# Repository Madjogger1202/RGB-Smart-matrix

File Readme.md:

# RGB-Matrix-SM16306

> 8×16 RGB LED matrix based on **SM16306SJ constant-current drivers**.  
> Designed as a cost-effective alternative to addressable LED panels.  

---

## Motivation
When working on a previous badge project, it became clear that building matrices out of addressable LEDs (e.g. WS2812) quickly becomes too expensive.  
The solution: use **standard RGB LEDs** combined with **constant-current drivers**.  

---

## Hardware Overview
- **LEDs**: XL-B1010RGBT-HF  
- **Matrix size**: 8 × 16 (128 RGB = 384 channels)  
- **Drivers**: SM16306SJ  
  - 16 constant-current channels per chip  
  - Current per channel: **20 mA**  
- **Row control**: standard shift register + power switches for row selection  
- **Power budget**:  
  - up to **34 LEDs per row**  
  - peak current up to **2 A per row**  

---

## Key Points
- At least **5× cheaper** compared to addressable LED matrices.  
- **Accurate current driving** ensures stable brightness and color balance.  
- Easily scalable for larger panels.  
- Requires an external **controller** (e.g. RP2040, ESP32) to drive shift registers and SM16306SJ chips.  

---

## PCB Notes
- Initial goal: a **two-sided layout**  
  - LEDs on the front  
  - Drivers + shift registers on the back  
- In practice: all components ended up on the same side to simplify routing.  
- Possible future version: **two-board design** (LED front panel + driver board).  

---

## Next Steps
- Integrate this matrix into the upcoming **badge version**.  
- Provide example firmware (SPI driving + timing).  
- Test long-term reliability at **20 mA per channel** load.  

---

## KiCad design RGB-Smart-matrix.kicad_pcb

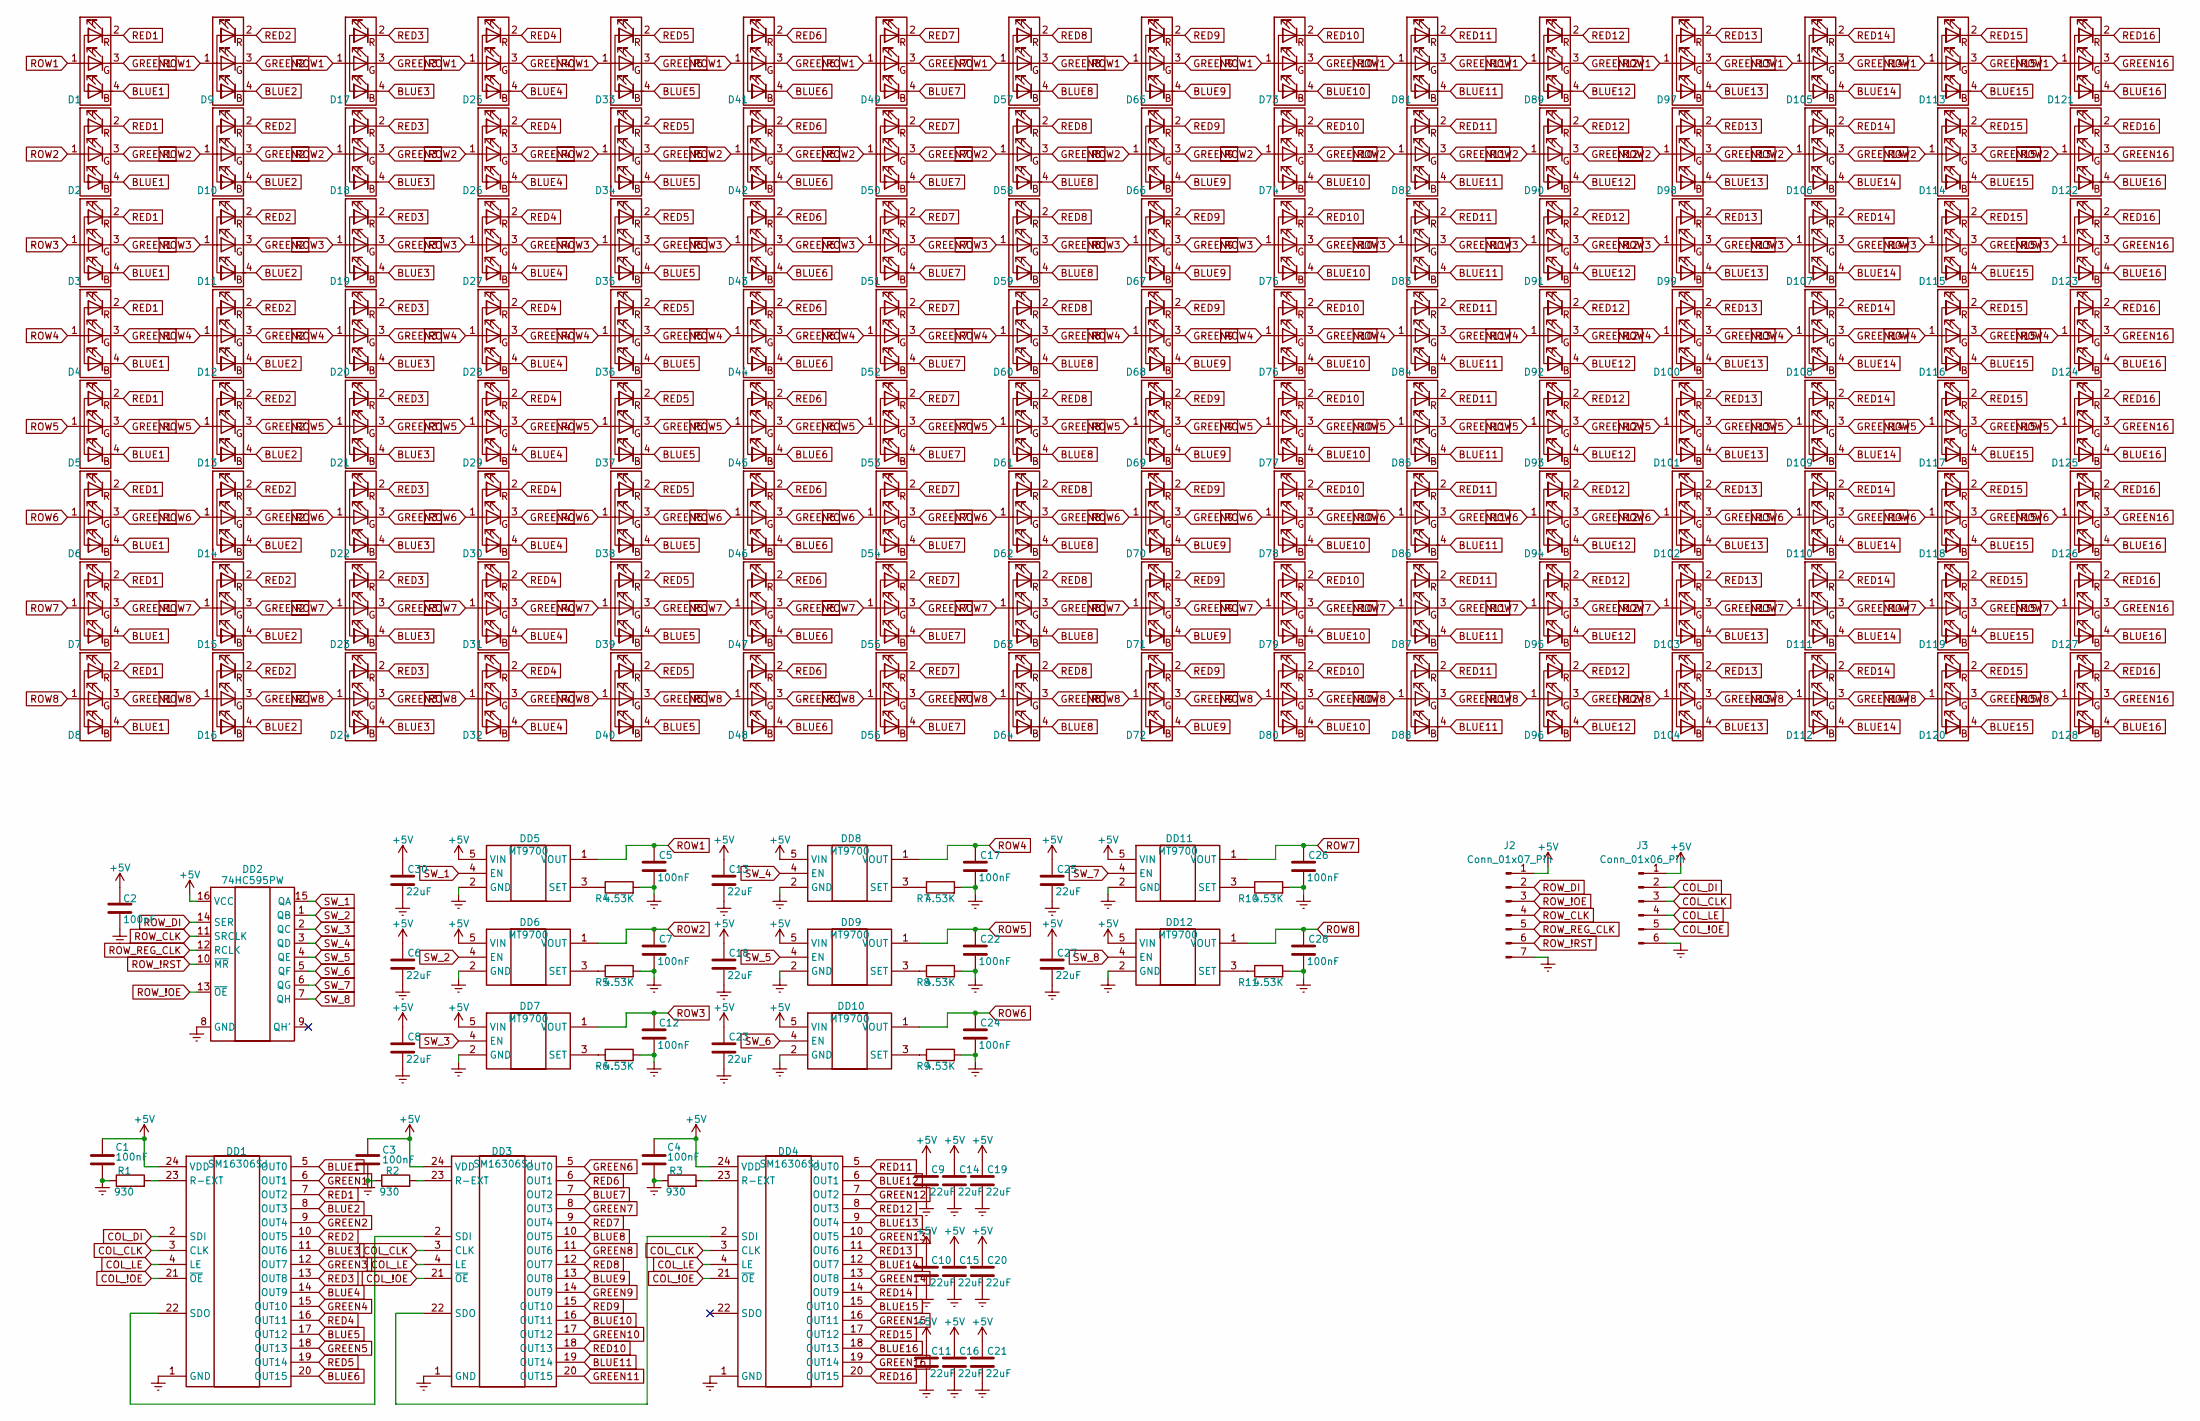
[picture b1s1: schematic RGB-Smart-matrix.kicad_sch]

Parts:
C1, C2, C3, C4, C5, C7, C12, C17, C22, C24, C26, C28: 100nF; C_0402_1005Metric
C6, C8, C9, C10, C11, C13, C14, C15, C16, C18, C19, C20, C21, C23, C25, C27, C30: 22uF; C_0402_1005Metric
D1, D2, D3, D4, D5, D6, D7, D8, D9, D10, D11, D12, D13, D14, D15, D16, D17, D18, D19, D20, D21, D22, D23, D24, D25, D26, D27, D28, D29, D30, D31, D32, D33, D34, D35, D36, D37, D38, D39, D40, D41, D42, D43, D44, D45, D46, D47, D48, D49, D50, D51, D52, D53, D54, D55, D56, D57, D58, D59, D60, D61, D62, D63, D64, D65, D66, D67, D68, D69, D70, D71, D72, D73, D74, D75, D76, D77, D78, D79, D80, D81, D82, D83, D84, D85, D86, D87, D88, D89, D90, D91, D92, D93, D94, D95, D96, D97, D98, D99, D100, D101, D102, D103, D104, D105, D106, D107, D108, D109, D110, D111, D112, D113, D114, D115, D116, D117, D118, D119, D120, D121, D122, D123, D124, D125, D126, D127, D128: XL-B1010RGBT-HF
DD1, DD3, DD4: SM16306SJ; Manufacturer_Part_Number SM16306SJ
DD2: 74HC595PW; TSSOP-16_4.4x5mm_P0.65mm
DD5, DD6, DD7, DD8, DD9, DD10, DD11, DD12: MT9700; Manufacturer_Part_Number MT9700
J2: Conn_01x07_Pin; PinHeader_1x07_P2.54mm_Vertical
J3: Conn_01x06_Pin; PinHeader_1x06_P2.54mm_Vertical
R1, R2, R3: 930; R_0402_1005Metric
R4, R5, R6, R7, R8, R9, R10, R11: 4.53K; R_0402_1005Metric

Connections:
+5V: C1.1, C2.1, C3.1, C4.1, C6.1, C8.1, C9.1, C10.1, C11.1, C13.1, C14.1, C15.1, C16.1, C18.1, C19.1, C20.1, C21.1, C23.1, C25.1, C27.1, C30.1, DD1.24 (VDD), DD2.16 (VCC), DD3.24 (VDD), DD4.24 (VDD), DD5.5 (VIN), DD6.5 (VIN), DD7.5 (VIN), DD8.5 (VIN), DD9.5 (VIN), DD10.5 (VIN), DD11.5 (VIN), DD12.5 (VIN), J2.1, J3.1
BLUE1: D1.4 (GA), D2.4 (GA), D3.4 (GA), D4.4 (GA), D5.4 (GA), D6.4 (GA), D7.4 (GA), D8.4 (GA), DD1.5 (OUT0)
BLUE2: D9.4 (GA), D10.4 (GA), D11.4 (GA), D12.4 (GA), D13.4 (GA), D14.4 (GA), D15.4 (GA), D16.4 (GA), DD1.8 (OUT3)
BLUE3: D17.4 (GA), D18.4 (GA), D19.4 (GA), D20.4 (GA), D21.4 (GA), D22.4 (GA), D23.4 (GA), D24.4 (GA), DD1.11 (OUT6)
BLUE4: D25.4 (GA), D26.4 (GA), D27.4 (GA), D28.4 (GA), D29.4 (GA), D30.4 (GA), D31.4 (GA), D32.4 (GA), DD1.14 (OUT9)
BLUE5: D33.4 (GA), D34.4 (GA), D35.4 (GA), D36.4 (GA), D37.4 (GA), D38.4 (GA), D39.4 (GA), D40.4 (GA), DD1.17 (OUT12)
BLUE6: D41.4 (GA), D42.4 (GA), D43.4 (GA), D44.4 (GA), D45.4 (GA), D46.4 (GA), D47.4 (GA), D48.4 (GA), DD1.20 (OUT15)
BLUE7: D49.4 (GA), D50.4 (GA), D51.4 (GA), D52.4 (GA), D53.4 (GA), D54.4 (GA), D55.4 (GA), D56.4 (GA), DD3.7 (OUT2)
BLUE8: D57.4 (GA), D58.4 (GA), D59.4 (GA), D60.4 (GA), D61.4 (GA), D62.4 (GA), D63.4 (GA), D64.4 (GA), DD3.10 (OUT5)
BLUE9: D65.4 (GA), D66.4 (GA), D67.4 (GA), D68.4 (GA), D69.4 (GA), D70.4 (GA), D71.4 (GA), D72.4 (GA), DD3.13 (OUT8)
BLUE10: D73.4 (GA), D74.4 (GA), D75.4 (GA), D76.4 (GA), D77.4 (GA), D78.4 (GA), D79.4 (GA), D80.4 (GA), DD3.16 (OUT11)
BLUE11: D81.4 (GA), D82.4 (GA), D83.4 (GA), D84.4 (GA), D85.4 (GA), D86.4 (GA), D87.4 (GA), D88.4 (GA), DD3.19 (OUT14)
BLUE12: D89.4 (GA), D90.4 (GA), D91.4 (GA), D92.4 (GA), D93.4 (GA), D94.4 (GA), D95.4 (GA), D96.4 (GA), DD4.6 (OUT1)
BLUE13: D97.4 (GA), D98.4 (GA), D99.4 (GA), D100.4 (GA), D101.4 (GA), D102.4 (GA), D103.4 (GA), D104.4 (GA), DD4.9 (OUT4)
BLUE14: D105.4 (GA), D106.4 (GA), D107.4 (GA), D108.4 (GA), D109.4 (GA), D110.4 (GA), D111.4 (GA), D112.4 (GA), DD4.12 (OUT7)
BLUE15: D113.4 (GA), D114.4 (GA), D115.4 (GA), D116.4 (GA), D117.4 (GA), D118.4 (GA), D119.4 (GA), D120.4 (GA), DD4.15 (OUT10)
BLUE16: D121.4 (GA), D122.4 (GA), D123.4 (GA), D124.4 (GA), D125.4 (GA), D126.4 (GA), D127.4 (GA), D128.4 (GA), DD4.18 (OUT13)
COL_!OE: DD1.21 (~OE), DD3.21 (~OE), DD4.21 (~OE), J3.5
COL_CLK: DD1.3 (CLK), DD3.3 (CLK), DD4.3 (CLK), J3.3
COL_DI: DD1.2 (SDI), J3.2
COL_LE: DD1.4 (LE), DD3.4 (LE), DD4.4 (LE), J3.4
Earth: C1.2, C2.2, C3.2, C4.2, C5.2, C6.2, C7.2, C8.2, C9.2, C10.2, C11.2, C12.2, C13.2, C14.2, C15.2, C16.2, C17.2, C18.2, C19.2, C20.2, C21.2, C22.2, C23.2, C24.2, C25.2, C26.2, C27.2, C28.2, C30.2, DD1.1 (GND), DD2.8 (GND), DD3.1 (GND), DD4.1 (GND), DD5.2 (GND), DD6.2 (GND), DD7.2 (GND), DD8.2 (GND), DD9.2 (GND), DD10.2 (GND), DD11.2 (GND), DD12.2 (GND), J2.7, J3.6, R1.1, R2.1, R3.1, R4.2, R5.2, R6.2, R7.2, R8.2, R9.2, R10.2, R11.2
GREEN1: D1.3 (BA), D2.3 (BA), D3.3 (BA), D4.3 (BA), D5.3 (BA), D6.3 (BA), D7.3 (BA), D8.3 (BA), DD1.6 (OUT1)
GREEN2: D9.3 (BA), D10.3 (BA), D11.3 (BA), D12.3 (BA), D13.3 (BA), D14.3 (BA), D15.3 (BA), D16.3 (BA), DD1.9 (OUT4)
GREEN3: D17.3 (BA), D18.3 (BA), D19.3 (BA), D20.3 (BA), D21.3 (BA), D22.3 (BA), D23.3 (BA), D24.3 (BA), DD1.12 (OUT7)
GREEN4: D25.3 (BA), D26.3 (BA), D27.3 (BA), D28.3 (BA), D29.3 (BA), D30.3 (BA), D31.3 (BA), D32.3 (BA), DD1.15 (OUT10)
GREEN5: D33.3 (BA), D34.3 (BA), D35.3 (BA), D36.3 (BA), D37.3 (BA), D38.3 (BA), D39.3 (BA), D40.3 (BA), DD1.18 (OUT13)
GREEN6: D41.3 (BA), D42.3 (BA), D43.3 (BA), D44.3 (BA), D45.3 (BA), D46.3 (BA), D47.3 (BA), D48.3 (BA), DD3.5 (OUT0)
GREEN7: D49.3 (BA), D50.3 (BA), D51.3 (BA), D52.3 (BA), D53.3 (BA), D54.3 (BA), D55.3 (BA), D56.3 (BA), DD3.8 (OUT3)
GREEN8: D57.3 (BA), D58.3 (BA), D59.3 (BA), D60.3 (BA), D61.3 (BA), D62.3 (BA), D63.3 (BA), D64.3 (BA), DD3.11 (OUT6)
GREEN9: D65.3 (BA), D66.3 (BA), D67.3 (BA), D68.3 (BA), D69.3 (BA), D70.3 (BA), D71.3 (BA), D72.3 (BA), DD3.14 (OUT9)
GREEN10: D73.3 (BA), D74.3 (BA), D75.3 (BA), D76.3 (BA), D77.3 (BA), D78.3 (BA), D79.3 (BA), D80.3 (BA), DD3.17 (OUT12)
GREEN11: D81.3 (BA), D82.3 (BA), D83.3 (BA), D84.3 (BA), D85.3 (BA), D86.3 (BA), D87.3 (BA), D88.3 (BA), DD3.20 (OUT15)
GREEN12: D89.3 (BA), D90.3 (BA), D91.3 (BA), D92.3 (BA), D93.3 (BA), D94.3 (BA), D95.3 (BA), D96.3 (BA), DD4.7 (OUT2)
GREEN13: D97.3 (BA), D98.3 (BA), D99.3 (BA), D100.3 (BA), D101.3 (BA), D102.3 (BA), D103.3 (BA), D104.3 (BA), DD4.10 (OUT5)
GREEN14: D105.3 (BA), D106.3 (BA), D107.3 (BA), D108.3 (BA), D109.3 (BA), D110.3 (BA), D111.3 (BA), D112.3 (BA), DD4.13 (OUT8)
GREEN15: D113.3 (BA), D114.3 (BA), D115.3 (BA), D116.3 (BA), D117.3 (BA), D118.3 (BA), D119.3 (BA), D120.3 (BA), DD4.16 (OUT11)
GREEN16: D121.3 (BA), D122.3 (BA), D123.3 (BA), D124.3 (BA), D125.3 (BA), D126.3 (BA), D127.3 (BA), D128.3 (BA), DD4.19 (OUT14)
unnamed: DD1.23 (R-EXT), R1.2
unnamed: DD1.22 (SDO), DD3.2 (SDI)
unnamed: DD3.23 (R-EXT), R2.2
unnamed: DD3.22 (SDO), DD4.2 (SDI)
unnamed: DD4.23 (R-EXT), R3.2
unnamed: DD5.3 (SET), R4.1
unnamed: DD6.3 (SET), R5.1
unnamed: DD7.3 (SET), R6.1
unnamed: DD8.3 (SET), R7.1
unnamed: DD9.3 (SET), R8.1
unnamed: DD10.3 (SET), R9.1
unnamed: DD11.3 (SET), R10.1
unnamed: DD12.3 (SET), R11.1
RED1: D1.2 (RA), D2.2 (RA), D3.2 (RA), D4.2 (RA), D5.2 (RA), D6.2 (RA), D7.2 (RA), D8.2 (RA), DD1.7 (OUT2)
RED2: D9.2 (RA), D10.2 (RA), D11.2 (RA), D12.2 (RA), D13.2 (RA), D14.2 (RA), D15.2 (RA), D16.2 (RA), DD1.10 (OUT5)
RED3: D17.2 (RA), D18.2 (RA), D19.2 (RA), D20.2 (RA), D21.2 (RA), D22.2 (RA), D23.2 (RA), D24.2 (RA), DD1.13 (OUT8)
RED4: D25.2 (RA), D26.2 (RA), D27.2 (RA), D28.2 (RA), D29.2 (RA), D30.2 (RA), D31.2 (RA), D32.2 (RA), DD1.16 (OUT11)
RED5: D33.2 (RA), D34.2 (RA), D35.2 (RA), D36.2 (RA), D37.2 (RA), D38.2 (RA), D39.2 (RA), D40.2 (RA), DD1.19 (OUT14)
RED6: D41.2 (RA), D42.2 (RA), D43.2 (RA), D44.2 (RA), D45.2 (RA), D46.2 (RA), D47.2 (RA), D48.2 (RA), DD3.6 (OUT1)
RED7: D49.2 (RA), D50.2 (RA), D51.2 (RA), D52.2 (RA), D53.2 (RA), D54.2 (RA), D55.2 (RA), D56.2 (RA), DD3.9 (OUT4)
RED8: D57.2 (RA), D58.2 (RA), D59.2 (RA), D60.2 (RA), D61.2 (RA), D62.2 (RA), D63.2 (RA), D64.2 (RA), DD3.12 (OUT7)
RED9: D65.2 (RA), D66.2 (RA), D67.2 (RA), D68.2 (RA), D69.2 (RA), D70.2 (RA), D71.2 (RA), D72.2 (RA), DD3.15 (OUT10)
RED10: D73.2 (RA), D74.2 (RA), D75.2 (RA), D76.2 (RA), D77.2 (RA), D78.2 (RA), D79.2 (RA), D80.2 (RA), DD3.18 (OUT13)
RED11: D81.2 (RA), D82.2 (RA), D83.2 (RA), D84.2 (RA), D85.2 (RA), D86.2 (RA), D87.2 (RA), D88.2 (RA), DD4.5 (OUT0)
RED12: D89.2 (RA), D90.2 (RA), D91.2 (RA), D92.2 (RA), D93.2 (RA), D94.2 (RA), D95.2 (RA), D96.2 (RA), DD4.8 (OUT3)
RED13: D97.2 (RA), D98.2 (RA), D99.2 (RA), D100.2 (RA), D101.2 (RA), D102.2 (RA), D103.2 (RA), D104.2 (RA), DD4.11 (OUT6)
RED14: D105.2 (RA), D106.2 (RA), D107.2 (RA), D108.2 (RA), D109.2 (RA), D110.2 (RA), D111.2 (RA), D112.2 (RA), DD4.14 (OUT9)
RED15: D113.2 (RA), D114.2 (RA), D115.2 (RA), D116.2 (RA), D117.2 (RA), D118.2 (RA), D119.2 (RA), D120.2 (RA), DD4.17 (OUT12)
RED16: D121.2 (RA), D122.2 (RA), D123.2 (RA), D124.2 (RA), D125.2 (RA), D126.2 (RA), D127.2 (RA), D128.2 (RA), DD4.20 (OUT15)
ROW1: C5.1, D1.1 (K), D9.1 (K), D17.1 (K), D25.1 (K), D33.1 (K), D41.1 (K), D49.1 (K), D57.1 (K), D65.1 (K), D73.1 (K), D81.1 (K), D89.1 (K), D97.1 (K), D105.1 (K), D113.1 (K), D121.1 (K), DD5.1 (VOUT)
ROW2: C7.1, D2.1 (K), D10.1 (K), D18.1 (K), D26.1 (K), D34.1 (K), D42.1 (K), D50.1 (K), D58.1 (K), D66.1 (K), D74.1 (K), D82.1 (K), D90.1 (K), D98.1 (K), D106.1 (K), D114.1 (K), D122.1 (K), DD6.1 (VOUT)
ROW3: C12.1, D3.1 (K), D11.1 (K), D19.1 (K), D27.1 (K), D35.1 (K), D43.1 (K), D51.1 (K), D59.1 (K), D67.1 (K), D75.1 (K), D83.1 (K), D91.1 (K), D99.1 (K), D107.1 (K), D115.1 (K), D123.1 (K), DD7.1 (VOUT)
ROW4: C17.1, D4.1 (K), D12.1 (K), D20.1 (K), D28.1 (K), D36.1 (K), D44.1 (K), D52.1 (K), D60.1 (K), D68.1 (K), D76.1 (K), D84.1 (K), D92.1 (K), D100.1 (K), D108.1 (K), D116.1 (K), D124.1 (K), DD8.1 (VOUT)
ROW5: C22.1, D5.1 (K), D13.1 (K), D21.1 (K), D29.1 (K), D37.1 (K), D45.1 (K), D53.1 (K), D61.1 (K), D69.1 (K), D77.1 (K), D85.1 (K), D93.1 (K), D101.1 (K), D109.1 (K), D117.1 (K), D125.1 (K), DD9.1 (VOUT)
ROW6: C24.1, D6.1 (K), D14.1 (K), D22.1 (K), D30.1 (K), D38.1 (K), D46.1 (K), D54.1 (K), D62.1 (K), D70.1 (K), D78.1 (K), D86.1 (K), D94.1 (K), D102.1 (K), D110.1 (K), D118.1 (K), D126.1 (K), DD10.1 (VOUT)
ROW7: C26.1, D7.1 (K), D15.1 (K), D23.1 (K), D31.1 (K), D39.1 (K), D47.1 (K), D55.1 (K), D63.1 (K), D71.1 (K), D79.1 (K), D87.1 (K), D95.1 (K), D103.1 (K), D111.1 (K), D119.1 (K), D127.1 (K), DD11.1 (VOUT)
ROW8: C28.1, D8.1 (K), D16.1 (K), D24.1 (K), D32.1 (K), D40.1 (K), D48.1 (K), D56.1 (K), D64.1 (K), D72.1 (K), D80.1 (K), D88.1 (K), D96.1 (K), D104.1 (K), D112.1 (K), D120.1 (K), D128.1 (K), DD12.1 (VOUT)
ROW_!OE: DD2.13 (~OE), J2.3
ROW_!RST: DD2.10 (~MR), J2.6
ROW_CLK: DD2.11 (SRCLK), J2.4
ROW_DI: DD2.14 (SER), J2.2
ROW_REG_CLK: DD2.12 (RCLK), J2.5
SW_1: DD2.15 (QA), DD5.4 (EN)
SW_2: DD2.1 (QB), DD6.4 (EN)
SW_3: DD2.2 (QC), DD7.4 (EN)
SW_4: DD2.3 (QD), DD8.4 (EN)
SW_5: DD2.4 (QE), DD9.4 (EN)
SW_6: DD2.5 (QF), DD10.4 (EN)
SW_7: DD2.6 (QG), DD11.4 (EN)
SW_8: DD2.7 (QH), DD12.4 (EN)

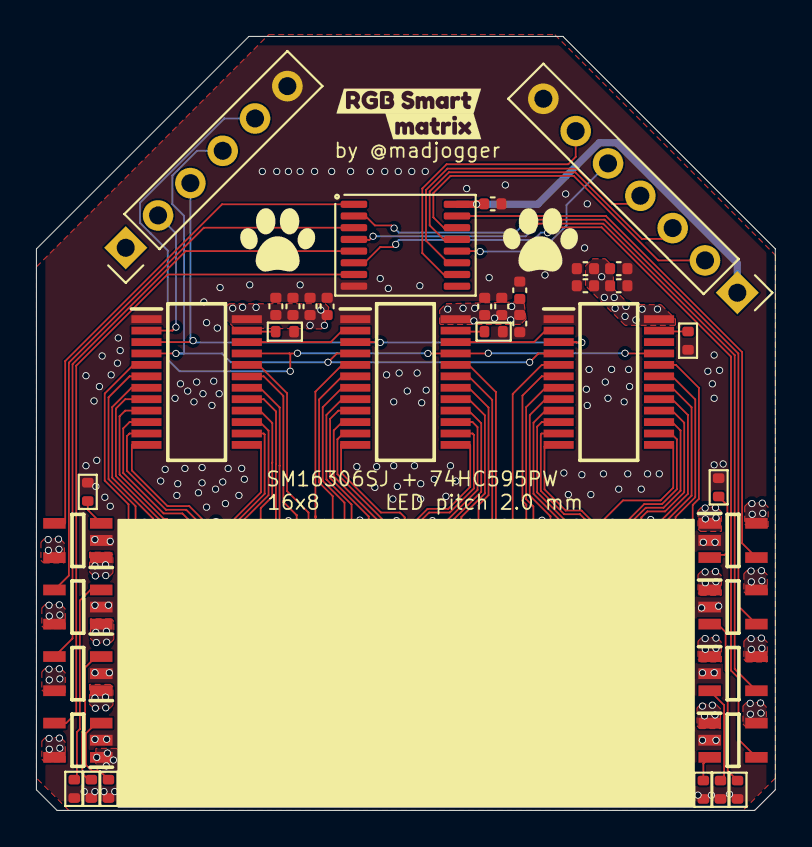
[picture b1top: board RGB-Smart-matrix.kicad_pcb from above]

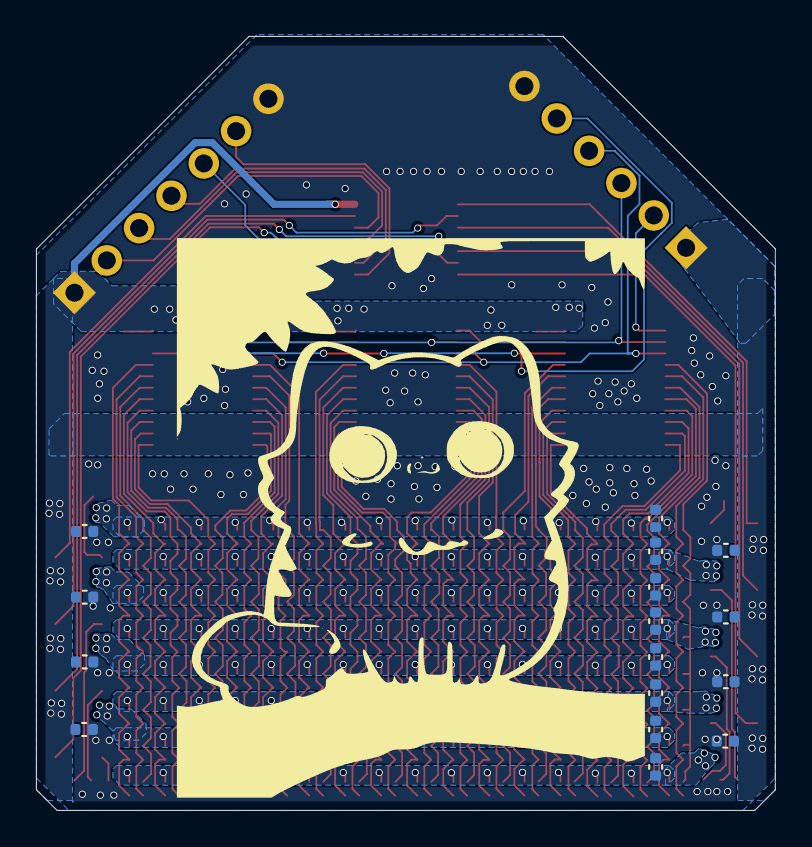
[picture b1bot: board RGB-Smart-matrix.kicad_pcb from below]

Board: 2 copper layers, 41.1 x 43.0 mm, 184 parts (16 on the bottom side), 88 nets.

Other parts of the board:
kibuzzard-68C5BC6D: G***; kibuzzard-68C5BC6D
kibuzzard-68C5BC7D: G***; kibuzzard-68C5BC7D

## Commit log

2025-09-13 rev0 ready
2025-09-13 drc fix
2025-09-15 Readme upd
